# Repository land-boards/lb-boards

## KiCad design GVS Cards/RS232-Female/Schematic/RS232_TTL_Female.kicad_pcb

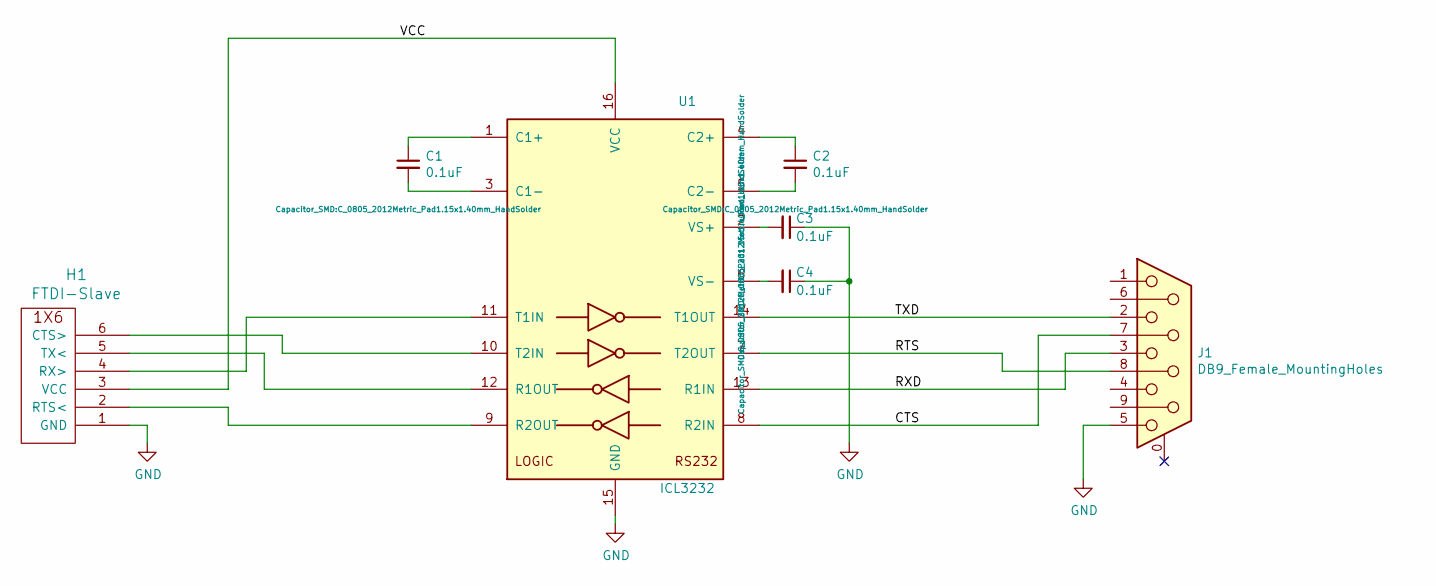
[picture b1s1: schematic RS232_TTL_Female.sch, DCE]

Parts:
C1, C2, C3, C4: 0.1uF; C_0805_2012Metric_Pad1.15x1.40mm_HandSolder
H1: FTDI-Slave
J1: DB9_Female_MountingHoles; DSUB-9_Female_Horizontal_P2.77x2.84mm_EdgePinOffset4.94mm_H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
U1: ICL3232; SOIC-16_3.9x9.9mm_P1.27mm

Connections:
/CTS: J1.7, U1.8 (R2IN)
/RTS: J1.8, U1.7 (T2OUT)
/RXD: J1.3, U1.13 (R1IN)
/TXD: J1.2, U1.14 (T1OUT)
/VCC: H1.3 (VCC), U1.16 (VCC)
GND: C3.1, C4.1, H1.1 (GND), J1.5, U1.15 (GND)
unnamed: C1.1, U1.1 (C1+)
unnamed: C1.2, U1.3 (C1-)
unnamed: C2.1, U1.4 (C2+)
unnamed: C2.2, U1.5 (C2-)
unnamed: C3.2, U1.2 (VS+)
unnamed: C4.2, U1.6 (VS-)
unnamed: H1.2 (RTS<), U1.9 (R2OUT)
unnamed: H1.4 (RX>), U1.11 (T1IN)
unnamed: H1.5 (TX<), U1.12 (R1OUT)
unnamed: H1.6 (CTS>), U1.10 (T2IN)

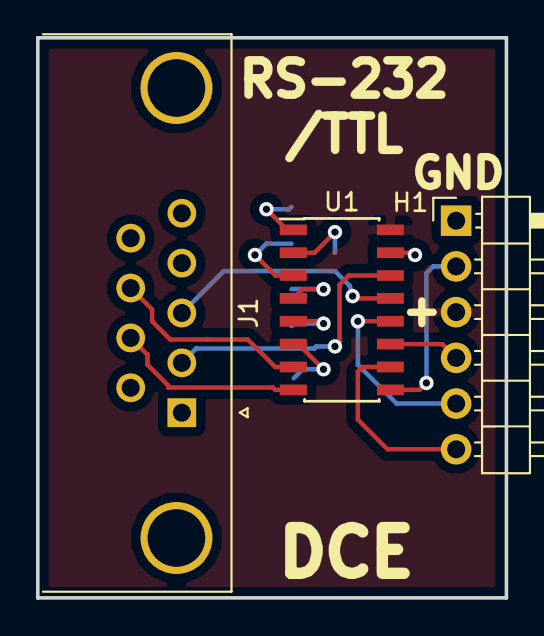
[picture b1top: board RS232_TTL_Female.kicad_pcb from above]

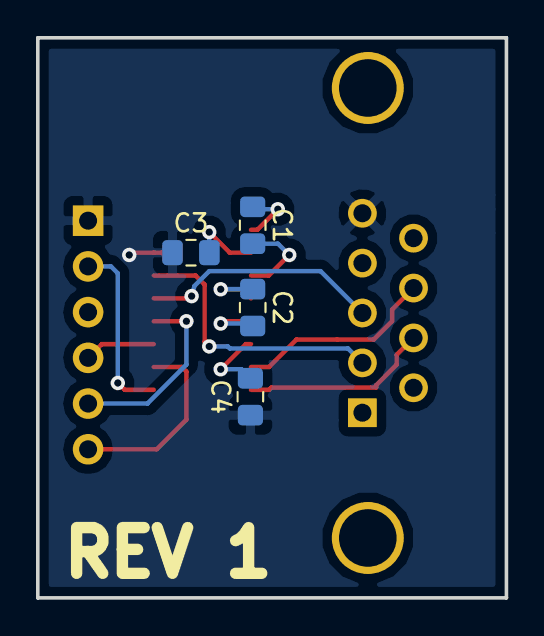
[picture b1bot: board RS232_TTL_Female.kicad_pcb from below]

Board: 2 copper layers, 26.0 x 31.1 mm, 7 parts (4 on the bottom side), 16 nets.

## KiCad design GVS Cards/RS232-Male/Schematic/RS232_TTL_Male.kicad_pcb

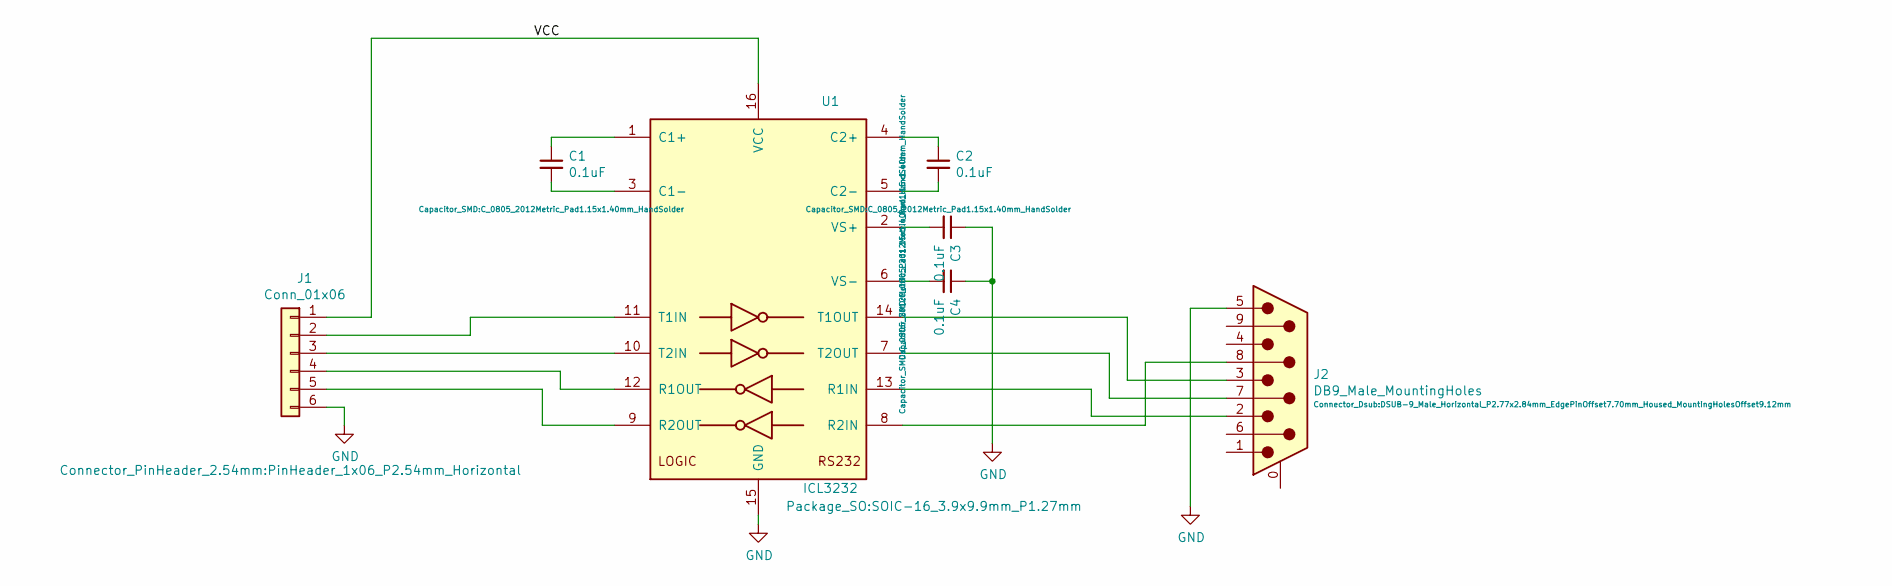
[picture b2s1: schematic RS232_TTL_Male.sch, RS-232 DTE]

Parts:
C1, C2, C3, C4: 0.1uF; C_0805_2012Metric_Pad1.15x1.40mm_HandSolder
J1: Conn_01x06; PinHeader_1x06_P2.54mm_Horizontal
J2: DB9_Male_MountingHoles; DSUB-9_Male_Horizontal_P2.77x2.84mm_EdgePinOffset7.70mm_Hou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
U1: ICL3232; SOIC-16_3.9x9.9mm_P1.27mm

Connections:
/VCC: J1.1, U1.16 (VCC)
GND: C3.1, C4.1, J1.6, J2.5, U1.15 (GND)
unnamed: C1.1, U1.1 (C1+)
unnamed: C1.2, U1.3 (C1-)
unnamed: C2.1, U1.4 (C2+)
unnamed: C2.2, U1.5 (C2-)
unnamed: C3.2, U1.2 (VS+)
unnamed: C4.2, U1.6 (VS-)
unnamed: J1.2, U1.11 (T1IN)
unnamed: J1.3, U1.10 (T2IN)
unnamed: J1.4, U1.12 (R1OUT)
unnamed: J1.5, U1.9 (R2OUT)
unnamed: J2.2, U1.13 (R1IN)
unnamed: J2.3, U1.14 (T1OUT)
unnamed: J2.7, U1.7 (T2OUT)
unnamed: J2.8, U1.8 (R2IN)

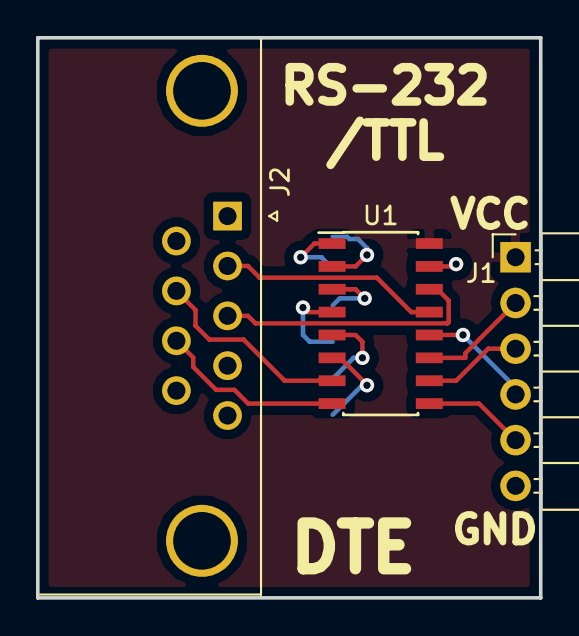
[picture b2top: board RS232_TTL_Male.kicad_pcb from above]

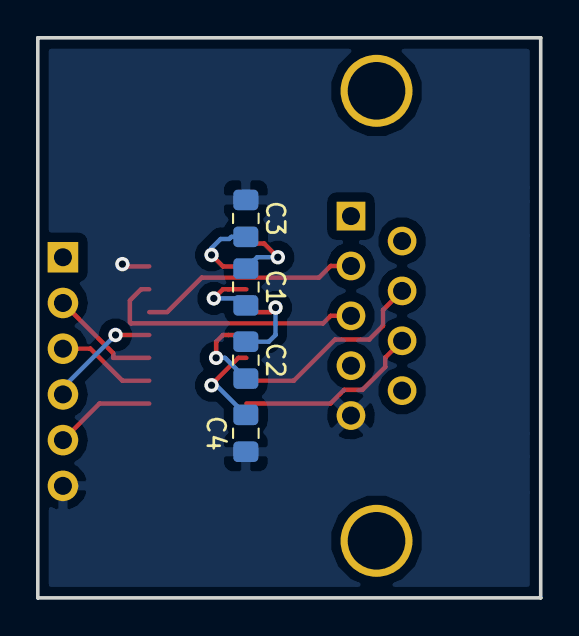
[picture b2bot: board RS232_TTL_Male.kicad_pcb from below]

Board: 2 copper layers, 27.9 x 31.1 mm, 7 parts (4 on the bottom side), 16 nets.

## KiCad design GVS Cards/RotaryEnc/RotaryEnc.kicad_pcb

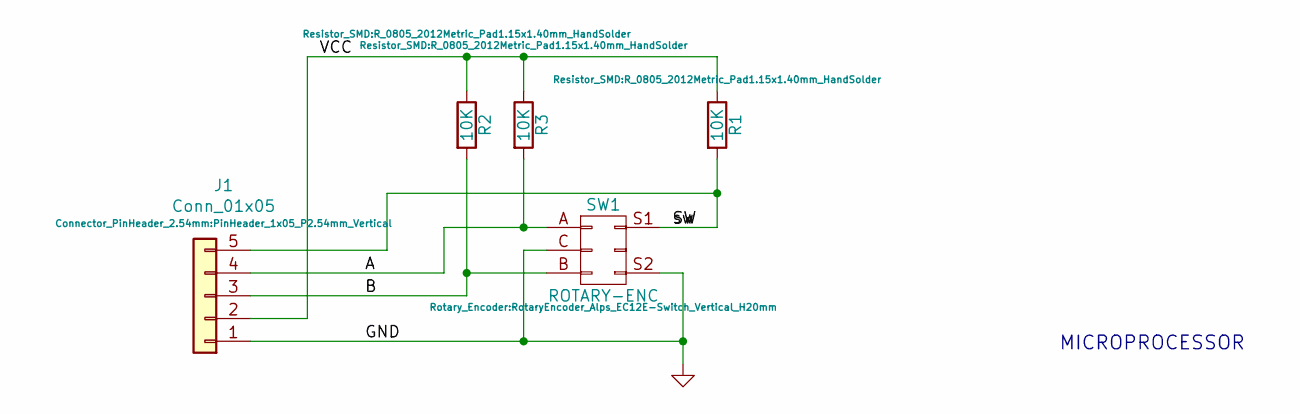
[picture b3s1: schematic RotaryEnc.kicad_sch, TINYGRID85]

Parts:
J1: Conn_01x05; PinHeader_1x05_P2.54mm_Vertical
R1, R2, R3: 10K; R_0805_2012Metric_Pad1.15x1.40mm_HandSolder
SW1: ROTARY-ENC; RotaryEncoder_Alps_EC12E-Switch_Vertical_H20mm

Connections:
/A: J1.4, R3.2, SW1.A
/B: J1.3, R2.2, SW1.B
/SW: J1.5, R1.2, SW1.S1
/VCC: J1.2, R1.1, R2.1, R3.1
GND: J1.1, SW1.C, SW1.S2

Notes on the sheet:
MICROPROCESSOR

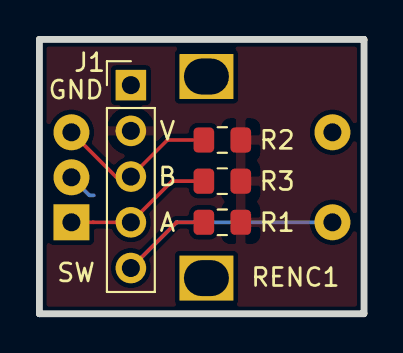
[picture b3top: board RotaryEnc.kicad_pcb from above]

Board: 2 copper layers, 18.0 x 15.2 mm, 5 parts (1 on the bottom side), 5 nets.

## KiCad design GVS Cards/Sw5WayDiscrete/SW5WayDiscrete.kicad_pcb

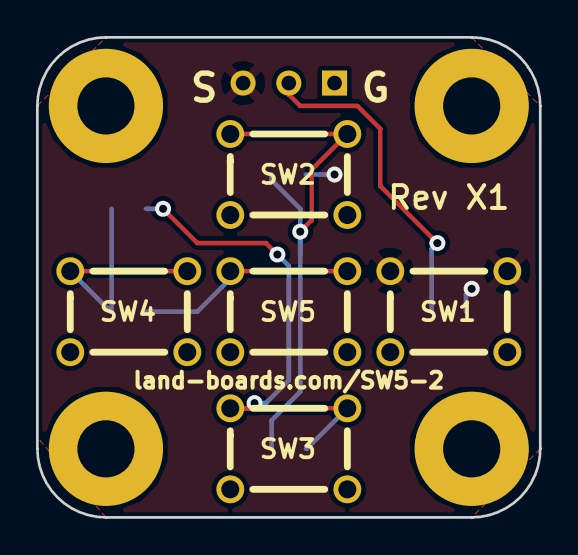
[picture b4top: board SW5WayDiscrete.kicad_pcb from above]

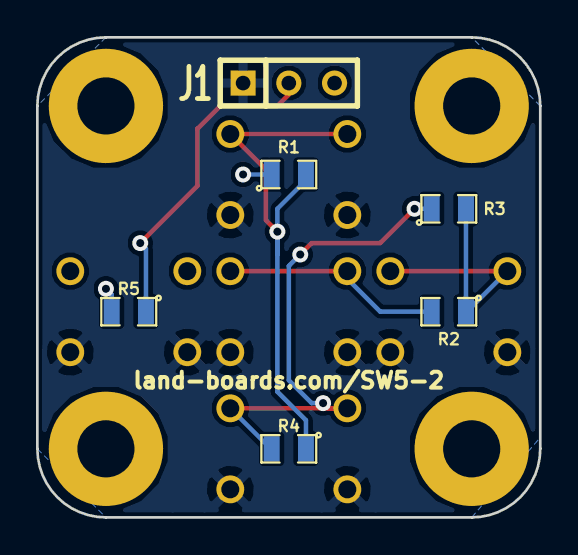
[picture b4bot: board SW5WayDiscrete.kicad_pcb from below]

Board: 2 copper layers, 27.9 x 26.7 mm, 15 parts (6 on the bottom side), 7 nets.

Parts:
J1: CONN_3; SIL-3
MTG1, MTG2, MTG3, MTG4: CONN_1; MTG-4-40
R1: 3.3K; SM0805
R2: 1K; SM0805
R3: 560; SM0805
R4: 330; SM0805
R5: 1.8K; SM0805
SW1, SW2, SW3, SW4, SW5: SW_PUSH_OMRON; SW-PB-6MM

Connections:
/GND: J1.1, SW1.1, SW1.2, SW2.1, SW2.2, SW3.1, SW3.2, SW4.1, SW4.2, SW5.1, SW5.2
/SIG: J1.3, R1.1, R5.2, SW1.3, SW1.4
/VCC: J1.2, R5.1
unnamed: R2.1, R3.2, SW4.3, SW4.4
unnamed: R3.1, R4.2, SW3.3, SW3.4
unnamed: R1.2, R4.1, SW2.3, SW2.4
unnamed: R2.2, SW5.3, SW5.4

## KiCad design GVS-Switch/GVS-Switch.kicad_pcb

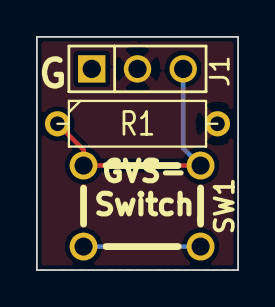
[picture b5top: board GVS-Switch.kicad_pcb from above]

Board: 2 copper layers, 11.2 x 13.0 mm, 3 parts (0 on the bottom side), 3 nets.

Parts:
J1: CONN_3; PIN_ARRAY_3X1
R1: 10K; R3-5
SW1: SW_PUSH_OMRON; SW-PB-6MM

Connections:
/GND: J1.1, SW1.3, SW1.4
/SIG: J1.3, R1.1, SW1.1, SW1.2
/VCC: J1.2, R1.2

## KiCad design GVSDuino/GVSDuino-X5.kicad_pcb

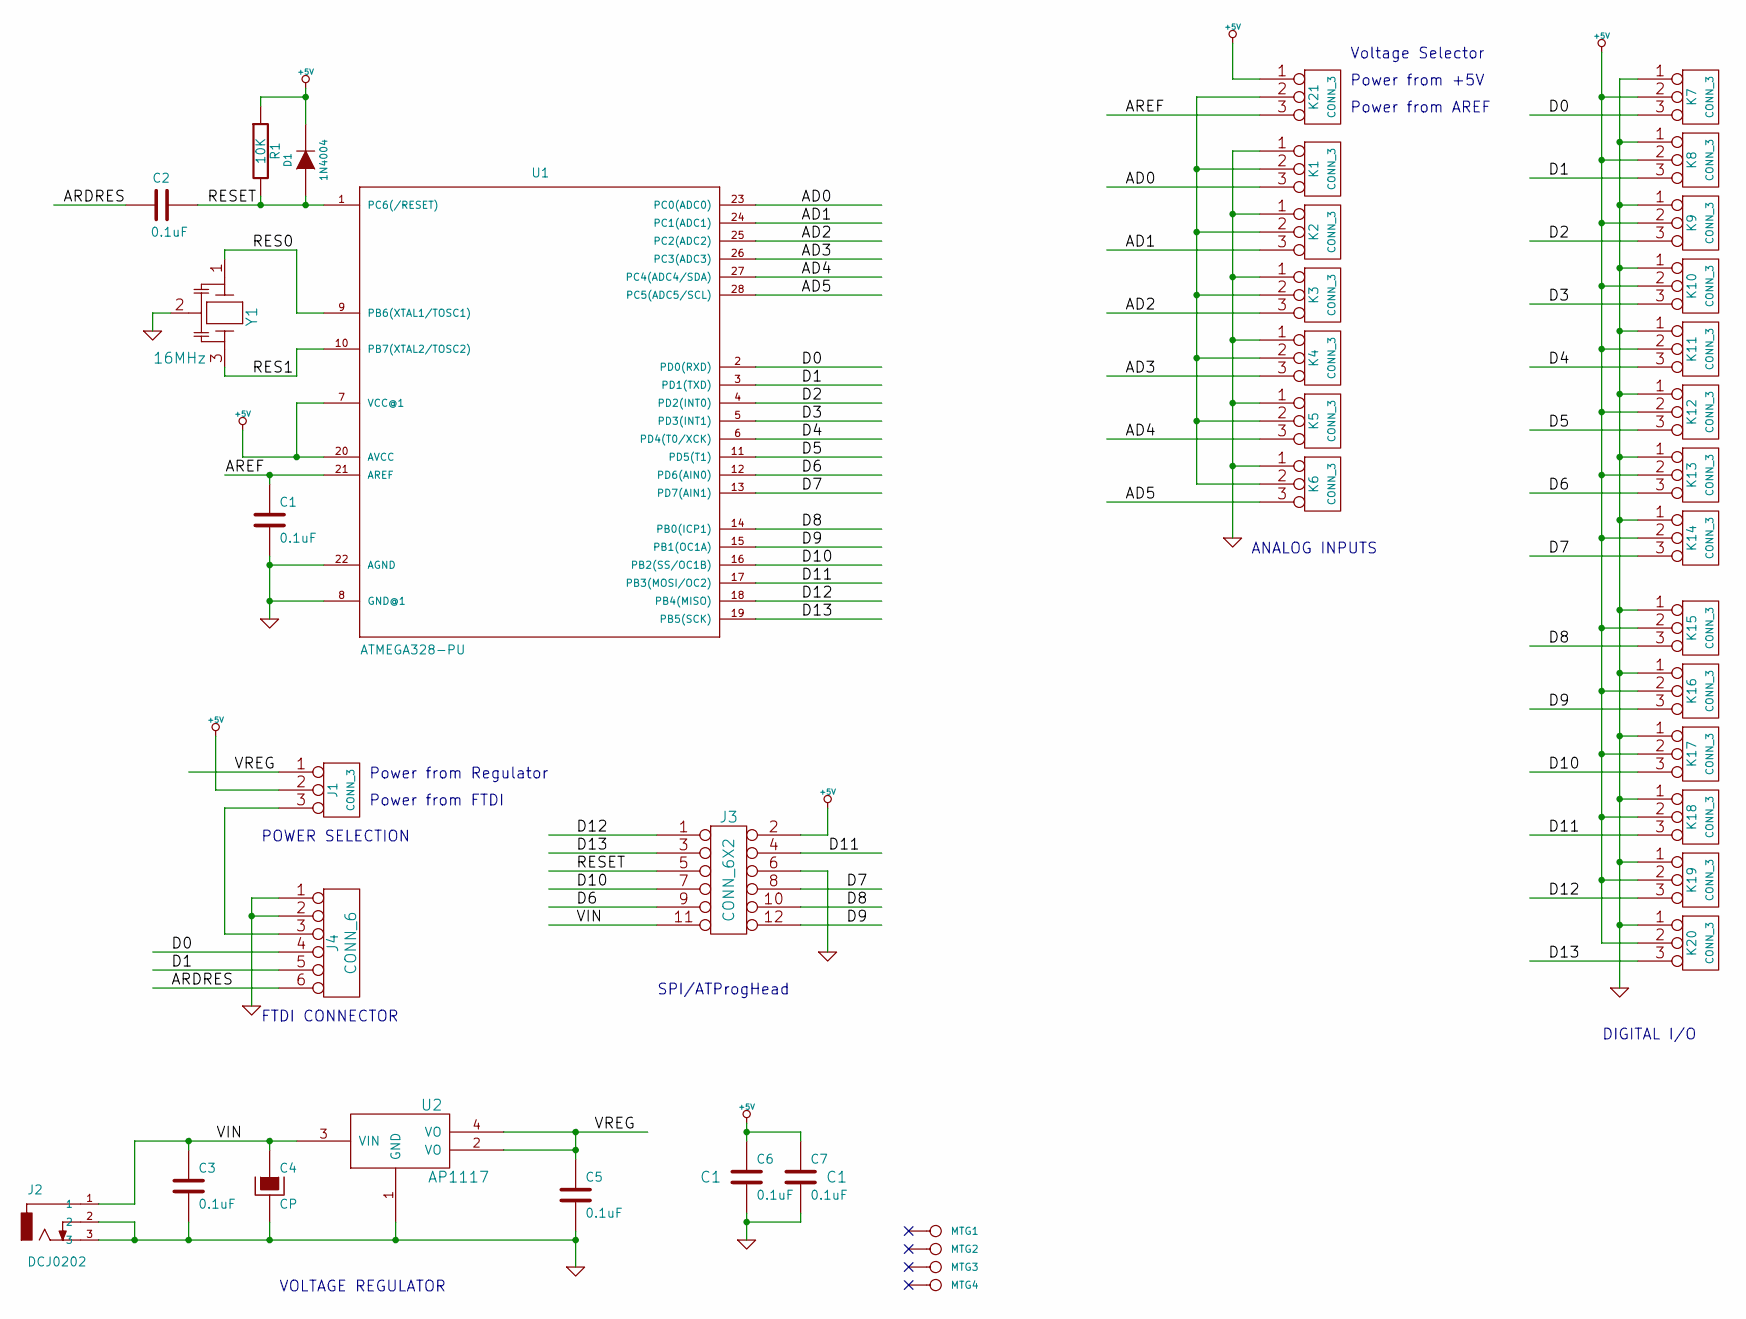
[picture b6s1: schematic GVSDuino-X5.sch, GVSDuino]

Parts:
C1, C2, C3, C5: 0.1uF
C4: CP
C6, C7: 0.1uF; C1
D1: 1N4004
J1: CONN_3
J2: DCJ0202; JACK-3.5MM
J3: CONN_6X2
J4: CONN_6
K1, K2, K3, K4, K5, K6, K7, K8, K9, K10, K11, K12, K13, K14, K15, K16, K17, K18, K19, K20, K21: CONN_3
MTG1, MTG2, MTG3, MTG4: CONN_1
R1: 10K
U1: ATMEGA328-PU; atmega8-DIL28-3
U2: AP1117
Y1: 16MHz

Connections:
+5V: C6.1, C7.1, D1.2 (K), J1.2 (PM), J3.2, K7.2 (PM), K8.2 (PM), K9.2 (PM), K10.2 (PM), K11.2 (PM), K12.2 (PM), K13.2 (PM), K14.2 (PM), K15.2 (PM), K16.2 (PM), K17.2 (PM), K18.2 (PM), K19.2 (PM), K20.2 (PM), K21.1, R1.1, U1.7 (VCC@1), U1.20 (AVCC)
/AD0: K1.3, U1.23 (PC0(ADC0))
/AD1: K2.3, U1.24 (PC1(ADC1))
/AD2: K3.3, U1.25 (PC2(ADC2))
/AD3: K4.3, U1.26 (PC3(ADC3))
/AD4: K5.3, U1.27 (PC4(ADC4/SDA))
/AD5: K6.3, U1.28 (PC5(ADC5/SCL))
/AREF: C1.1, K21.3, U1.21 (AREF)
/D0: J4.4, K7.3, U1.2 (PD0(RXD))
/D1: J4.5, K8.3, U1.3 (PD1(TXD))
/D2: K9.3, U1.4 (PD2(INT0))
/D3: K10.3, U1.5 (PD3(INT1))
/D4: K11.3, U1.6 (PD4(T0/XCK))
/D5: K12.3, U1.11 (PD5(T1))
/D6: J3.9, K13.3, U1.12 (PD6(AIN0))
/D7: J3.8, K14.3, U1.13 (PD7(AIN1))
/D8: J3.10, K15.3, U1.14 (PB0(ICP1))
/D9: J3.12, K16.3, U1.15 (PB1(OC1A))
/D10: J3.7, K17.3, U1.16 (PB2(SS/OC1B))
/D11: J3.4, K18.3, U1.17 (PB3(MOSI/OC2))
/D12: J3.1, K19.3, U1.18 (PB4(MISO))
/D13: J3.3, K20.3, U1.19 (PB5(SCK))
/FTDIRES: C2.1, J4.6
/RES0: U1.9 (PB6(XTAL1/TOSC1)), Y1.1
/RES1: U1.10 (PB7(XTAL2/TOSC2)), Y1.3
/RESET: C2.2, D1.1 (A), J3.5, R1.2, U1.1 (PC6(/RESET))
/VIN: C3.1, C4.1, J2.1, J3.11, U2.3 (VIN)
/VREG: C5.1, J1.1, U2.2 (VO), U2.4 (VO)
GND: C1.2, C3.2, C4.2, C5.2, C6.2, C7.2, J2.2, J2.3, J3.6, J4.1, J4.2, K1.1, K2.1, K3.1, K4.1, K5.1, K6.1, K7.1, K8.1, K9.1, K10.1, K11.1, K12.1, K13.1, K14.1, K15.1, K16.1, K17.1, K18.1, K19.1, K20.1, U1.8 (GND@1), U1.22 (AGND), U2.1 (GND), Y1.2
unnamed: J1.3, J4.3
unnamed: K1.2 (PM), K2.2 (PM), K3.2 (PM), K4.2 (PM), K5.2 (PM), K6.2 (PM), K21.2 (PM)

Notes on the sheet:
FTDI CONNECTOR
POWER SELECTION
ANALOG INPUTS
Voltage Selector
Power from +5V
Power from AREF
DIGITAL I/O
SPI/ATProgHead
VOLTAGE REGULATOR
Power from Regulator
Power from FTDI

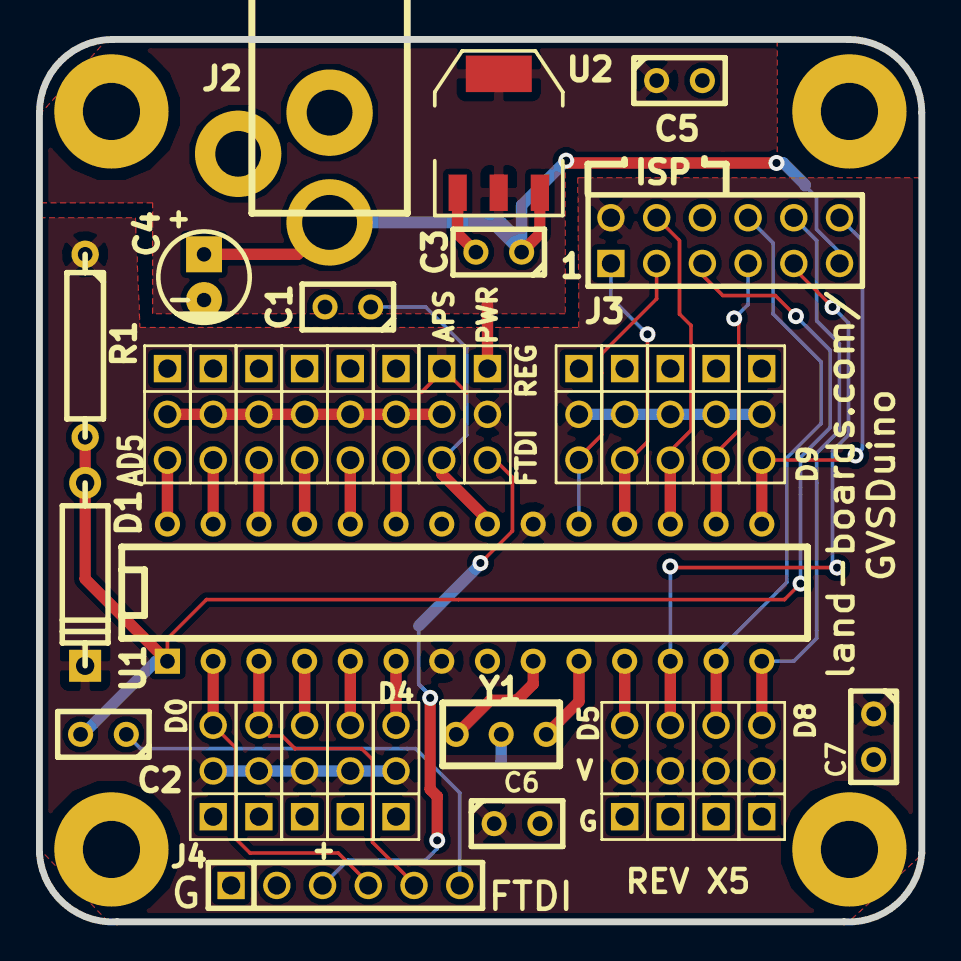
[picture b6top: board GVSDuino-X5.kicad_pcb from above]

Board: 2 copper layers, 49.0 x 49.0 mm, 42 parts (0 on the bottom side), 31 nets.

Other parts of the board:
TESTED: VAL**; TEST_BLK-REAR
